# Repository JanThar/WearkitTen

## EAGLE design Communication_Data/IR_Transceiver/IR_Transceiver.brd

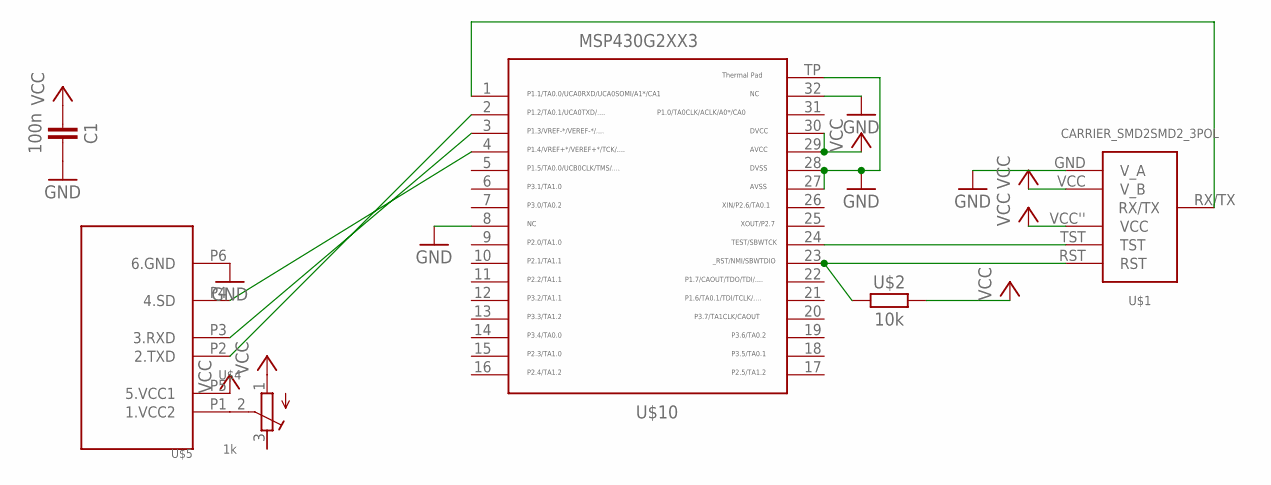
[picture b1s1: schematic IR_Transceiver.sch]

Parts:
C1: 100n; 603
U$1: CARRIER_SMD2SMD2_3POL; CARRIER_SMD2_3POL
U$2: 10k; 603
U$4: 1k; POTI35
U$5: TFBS4711
U$10: MSP430G2553; QFN32

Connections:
GND: C1.2, U$1.GND (V_A), U$5.P6 (6.GND), U$10.8, U$10.27, U$10.28, U$10.32, U$10.TP
unnamed: U$4.2 (S), U$5.P1 (1.VCC2)
unnamed: U$1.TST, U$10.24
unnamed: U$1.RST, U$2.1, U$10.23
unnamed: U$5.P2 (2.TXD), U$10.2
unnamed: U$5.P3 (3.RXD), U$10.3
unnamed: U$5.P4 (4.SD), U$10.4
unnamed: U$1.RX/TX, U$10.1
VCC: C1.1, U$1.VCC (V_B), U$1.VCC'' (VCC), U$2.2, U$4.1 (A), U$5.P5 (5.VCC1), U$10.29, U$10.30

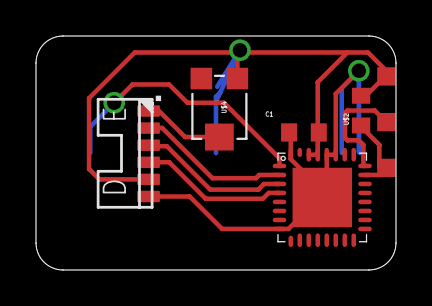
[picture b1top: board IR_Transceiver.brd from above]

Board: 2 copper layers, 20.0 x 13.0 mm, 6 parts (0 on the bottom side), 9 nets.

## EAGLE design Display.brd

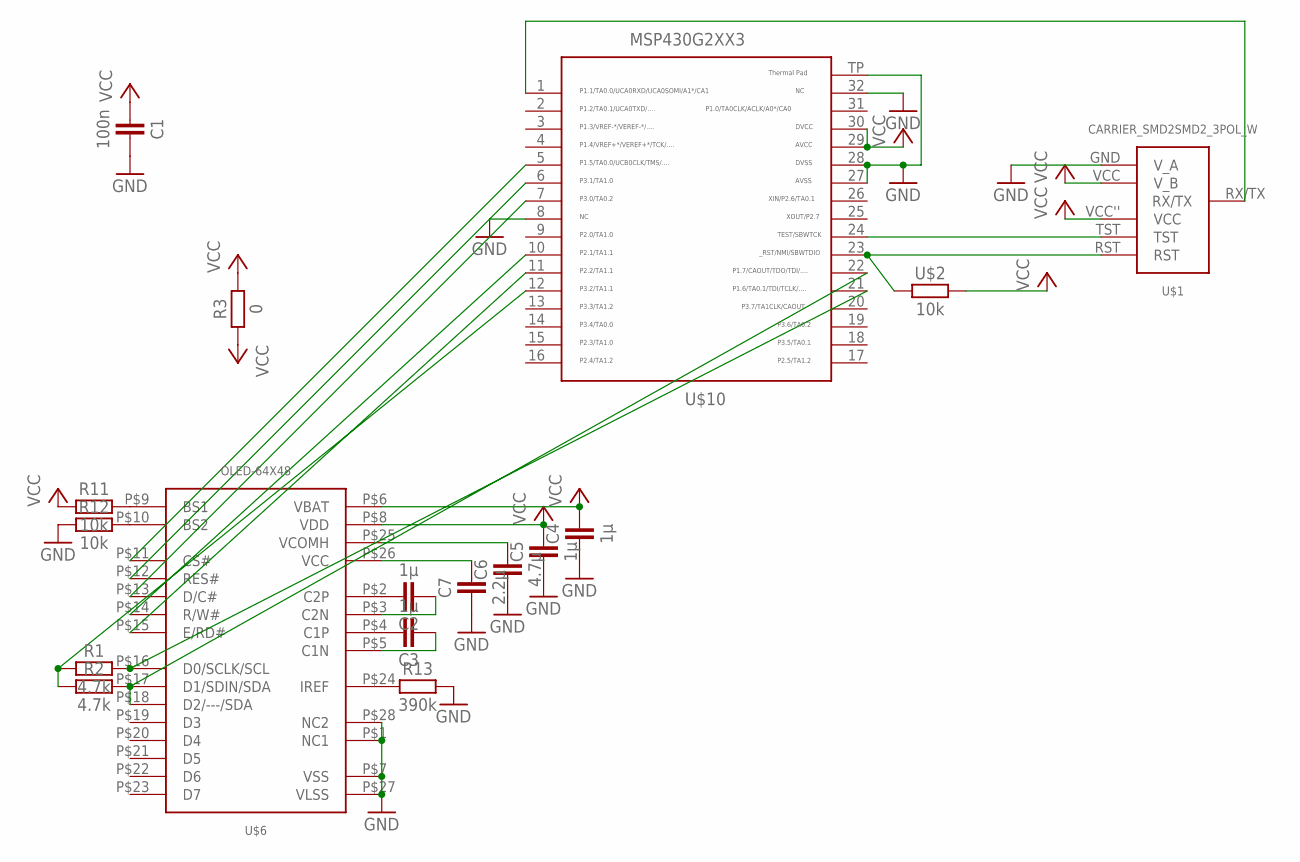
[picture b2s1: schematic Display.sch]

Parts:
C1: 100n; 603
C2, C3, C4, C5: 1µ; 603
C6: 4.7µ; 603
C7: 2.2µ; 603
R1, R2: 4.7k; 603
R3: 0; 603
R11, R12: 10k; 603
R13: 390k; 603
U$1: CARRIER_SMD2SMD2_3POL_W; CARRIER_SMD2_WIDE_3POL
U$2: 10k; 603
U$6: OLED-64X48; OLED_DISPLAY
U$10: MSP430G2553; QFN32

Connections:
GND: C1.2, C4.1, C5.1, C6.1, C7.1, R12.1, R13.2, U$1.GND (V_A), U$6.P$1 (NC1), U$6.P$7 (VSS), U$6.P$27 (VLSS), U$6.P$28 (NC2), U$10.8, U$10.27, U$10.28, U$10.32, U$10.TP
unnamed: R1.2, U$6.P$16 (D0/SCLK/SCL), U$10.21
unnamed: U$1.TST, U$10.24
unnamed: U$1.RST, U$2.1, U$10.23
unnamed: U$6.P$11 (CS#), U$10.5
unnamed: U$6.P$12 (RES#), U$10.6
unnamed: R2.2, U$6.P$17 (D1/SDIN/SDA), U$6.P$18 (D2/---/SDA), U$10.22
unnamed: U$6.P$13 (D/C#), U$10.7
unnamed: U$1.RX/TX, U$10.1
unnamed: R11.2, U$6.P$9 (BS1)
unnamed: R12.2, U$6.P$10 (BS2)
unnamed: R13.1, U$6.P$24 (IREF)
unnamed: C2.2, U$6.P$2 (C2P)
unnamed: C3.2, U$6.P$4 (C1P)
unnamed: C3.1, U$6.P$5 (C1N)
unnamed: C2.1, U$6.P$3 (C2N)
unnamed: U$6.P$14 (R/W#), U$10.10
unnamed: U$6.P$15 (E/RD#), U$10.11
unnamed: R1.1, R2.1, U$10.12
unnamed: C7.2, U$6.P$26 (VCC)
unnamed: C6.2, U$6.P$25 (VCOMH)
VCC: C1.1, C4.2, C5.2, R3.1, R3.2, R11.1, U$1.VCC (V_B), U$1.VCC'' (VCC), U$2.2, U$6.P$6 (VBAT), U$6.P$8 (VDD), U$10.29, U$10.30

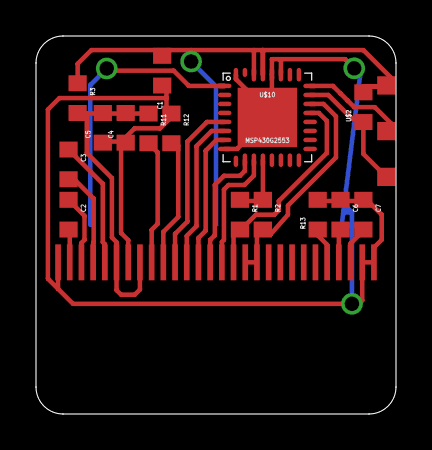
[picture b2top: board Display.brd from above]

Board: 2 copper layers, 20.0 x 21.0 mm, 17 parts (0 on the bottom side), 22 nets.

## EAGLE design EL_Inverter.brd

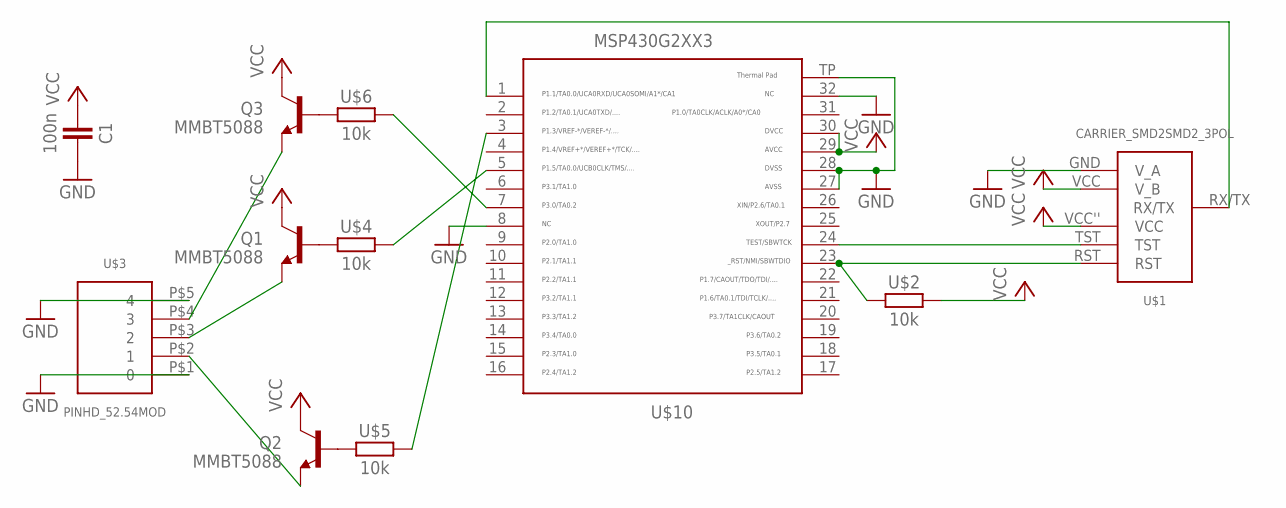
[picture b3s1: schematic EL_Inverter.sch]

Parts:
C1: 100n; 603
Q1, Q2, Q3: MMBT5088; SOT23-3
U$1: CARRIER_SMD2SMD2_3POL; CARRIER_SMD2_3POL
U$2, U$4, U$5, U$6: 10k; 603
U$3: PINHD_52.54MOD; PINHD_5_MOD
U$10: MSP430G2553; QFN32

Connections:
GND: C1.2, U$1.GND (V_A), U$3.P$1 (0), U$3.P$5 (4), U$10.8, U$10.27, U$10.28, U$10.32, U$10.TP
unnamed: Q1.1 (B), U$4.1
unnamed: U$1.TST, U$10.24
unnamed: U$1.RST, U$2.1, U$10.23
unnamed: Q2.1 (B), U$5.1
unnamed: Q2.2 (E), U$3.P$2 (1)
unnamed: Q1.2 (E), U$3.P$3 (2)
unnamed: Q3.1 (B), U$6.1
unnamed: U$1.RX/TX, U$10.1
unnamed: Q3.2 (E), U$3.P$4 (3)
unnamed: U$5.2, U$10.3
unnamed: U$4.2, U$10.5
unnamed: U$6.2, U$10.7
VCC: C1.1, Q1.3 (C), Q2.3 (C), Q3.3 (C), U$1.VCC (V_B), U$1.VCC'' (VCC), U$2.2, U$10.29, U$10.30

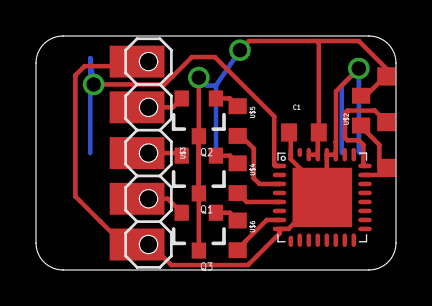
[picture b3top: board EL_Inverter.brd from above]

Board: 2 copper layers, 20.0 x 13.0 mm, 11 parts (0 on the bottom side), 14 nets.

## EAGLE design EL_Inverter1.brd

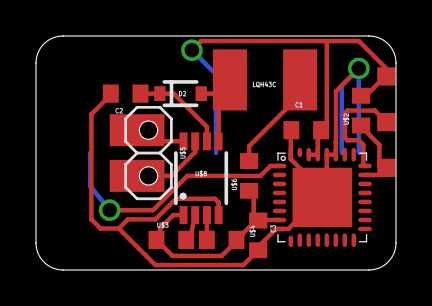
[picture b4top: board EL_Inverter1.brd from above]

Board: 2 copper layers, 20.0 x 13.0 mm, 13 parts (0 on the bottom side), 13 nets.

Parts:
C1: 100n; 603
C2: 2.7n; 603
C3: 2.2µ; 603
D2: 250mA/100V; SOD-323
LQH43C: 220µ; L1812
U$1: CARRIER_SMD2SMD2_3POL; CARRIER_SMD2_3POL
U$2: 10k; 603
U$3: 332; 603
U$4: 1.78M; 603
U$5: PINHD_22.54MOD; PINHD_2_MOD
U$6: 0; 603
U$8: MIC4830; MSOP8
U$10: MSP430G2553; QFN32

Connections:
GND: C1.2, C2.1, C3.2, U$1.GND, U$8.4, U$10.8, U$10.27, U$10.28, U$10.32, U$10.TP
unnamed: U$3.2, U$8.2
unnamed: U$1.TST, U$10.24
unnamed: U$1.RST, U$2.1, U$10.23
unnamed: U$4.2, U$8.3
unnamed: C2.2, D2.C, U$8.6
unnamed: D2.A, LQH43C.2, U$8.5
unnamed: LQH43C.1, U$6.2
unnamed: U$1.RX/TX, U$10.1
unnamed: C3.1, U$3.1, U$4.1, U$6.1, U$8.1, U$10.7
unnamed: U$5.P$1, U$8.8
unnamed: U$5.P$2, U$8.7
VCC: C1.1, U$1.VCC, U$1.VCC'', U$2.2, U$10.29, U$10.30

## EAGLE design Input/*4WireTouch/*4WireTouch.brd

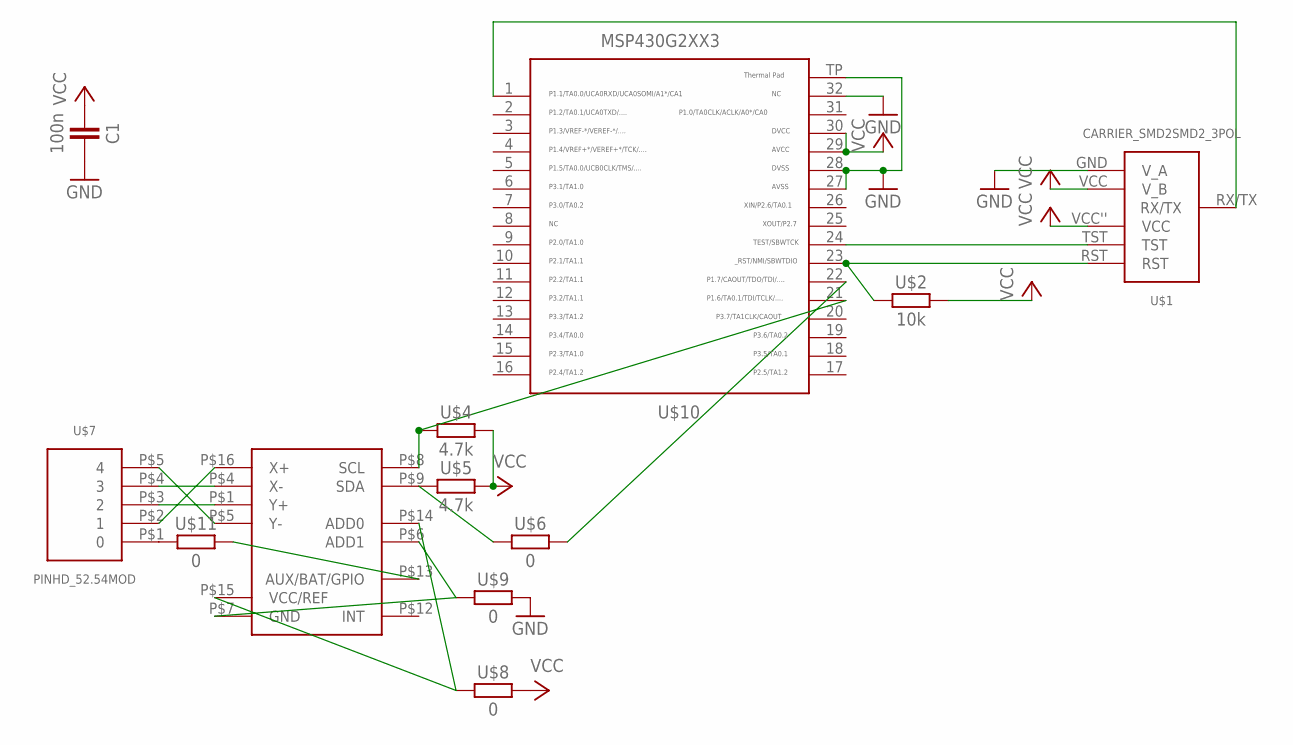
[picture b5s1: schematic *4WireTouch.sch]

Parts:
C1: 100n; 603
U$1: CARRIER_SMD2SMD2_3POL; CARRIER_SMD2_3POL
U$2: 10k; 603
U$3: AD7879; LFCSP
U$4, U$5: 4.7k; 603
U$6, U$8, U$9, U$11: 0; 603
U$7: PINHD_52.54MOD; PINHD_5_MOD
U$10: MSP430G2553; QFN32

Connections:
GND: C1.2, U$1.GND (V_A), U$9.2, U$10.27, U$10.28, U$10.32, U$10.TP
unnamed: U$3.P$8 (SCL), U$4.1, U$10.21
unnamed: U$1.TST, U$10.24
unnamed: U$1.RST, U$2.1, U$10.23
unnamed: U$3.P$9 (SDA), U$5.1, U$6.1
unnamed: U$7.P$1 (0), U$11.1
unnamed: U$3.P$16 (X+), U$7.P$2 (1)
unnamed: U$3.P$1 (Y+), U$7.P$3 (2)
unnamed: U$1.RX/TX, U$10.1
unnamed: U$3.P$4 (X-), U$7.P$4 (3)
unnamed: U$3.P$5 (Y-), U$7.P$5 (4)
unnamed: U$6.2, U$10.22
unnamed: U$3.P$14 (ADD0), U$3.P$15 (VCC/REF), U$8.1
unnamed: U$3.P$6 (ADD1), U$3.P$7 (GND), U$9.1
unnamed: U$3.P$13 (AUX/BAT/GPIO), U$11.2
VCC: C1.1, U$1.VCC (V_B), U$1.VCC'' (VCC), U$2.2, U$4.2, U$5.2, U$8.2, U$10.29, U$10.30

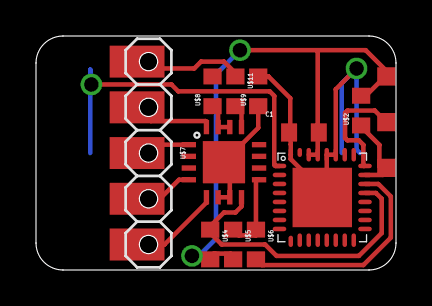
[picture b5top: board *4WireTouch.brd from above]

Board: 2 copper layers, 20.0 x 13.0 mm, 12 parts (0 on the bottom side), 16 nets.

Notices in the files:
parts and their libraries:
SparkFun-DiscreteSemi: Licensing: Creative Commons ShareAlike 4.0 International - https://creativecommons.org/licenses/by-sa/4.0
SparkFun-DiscreteSemi: Licensing: CC v3.0 Share-Alike You are welcome to use this library for commercial purposes.
